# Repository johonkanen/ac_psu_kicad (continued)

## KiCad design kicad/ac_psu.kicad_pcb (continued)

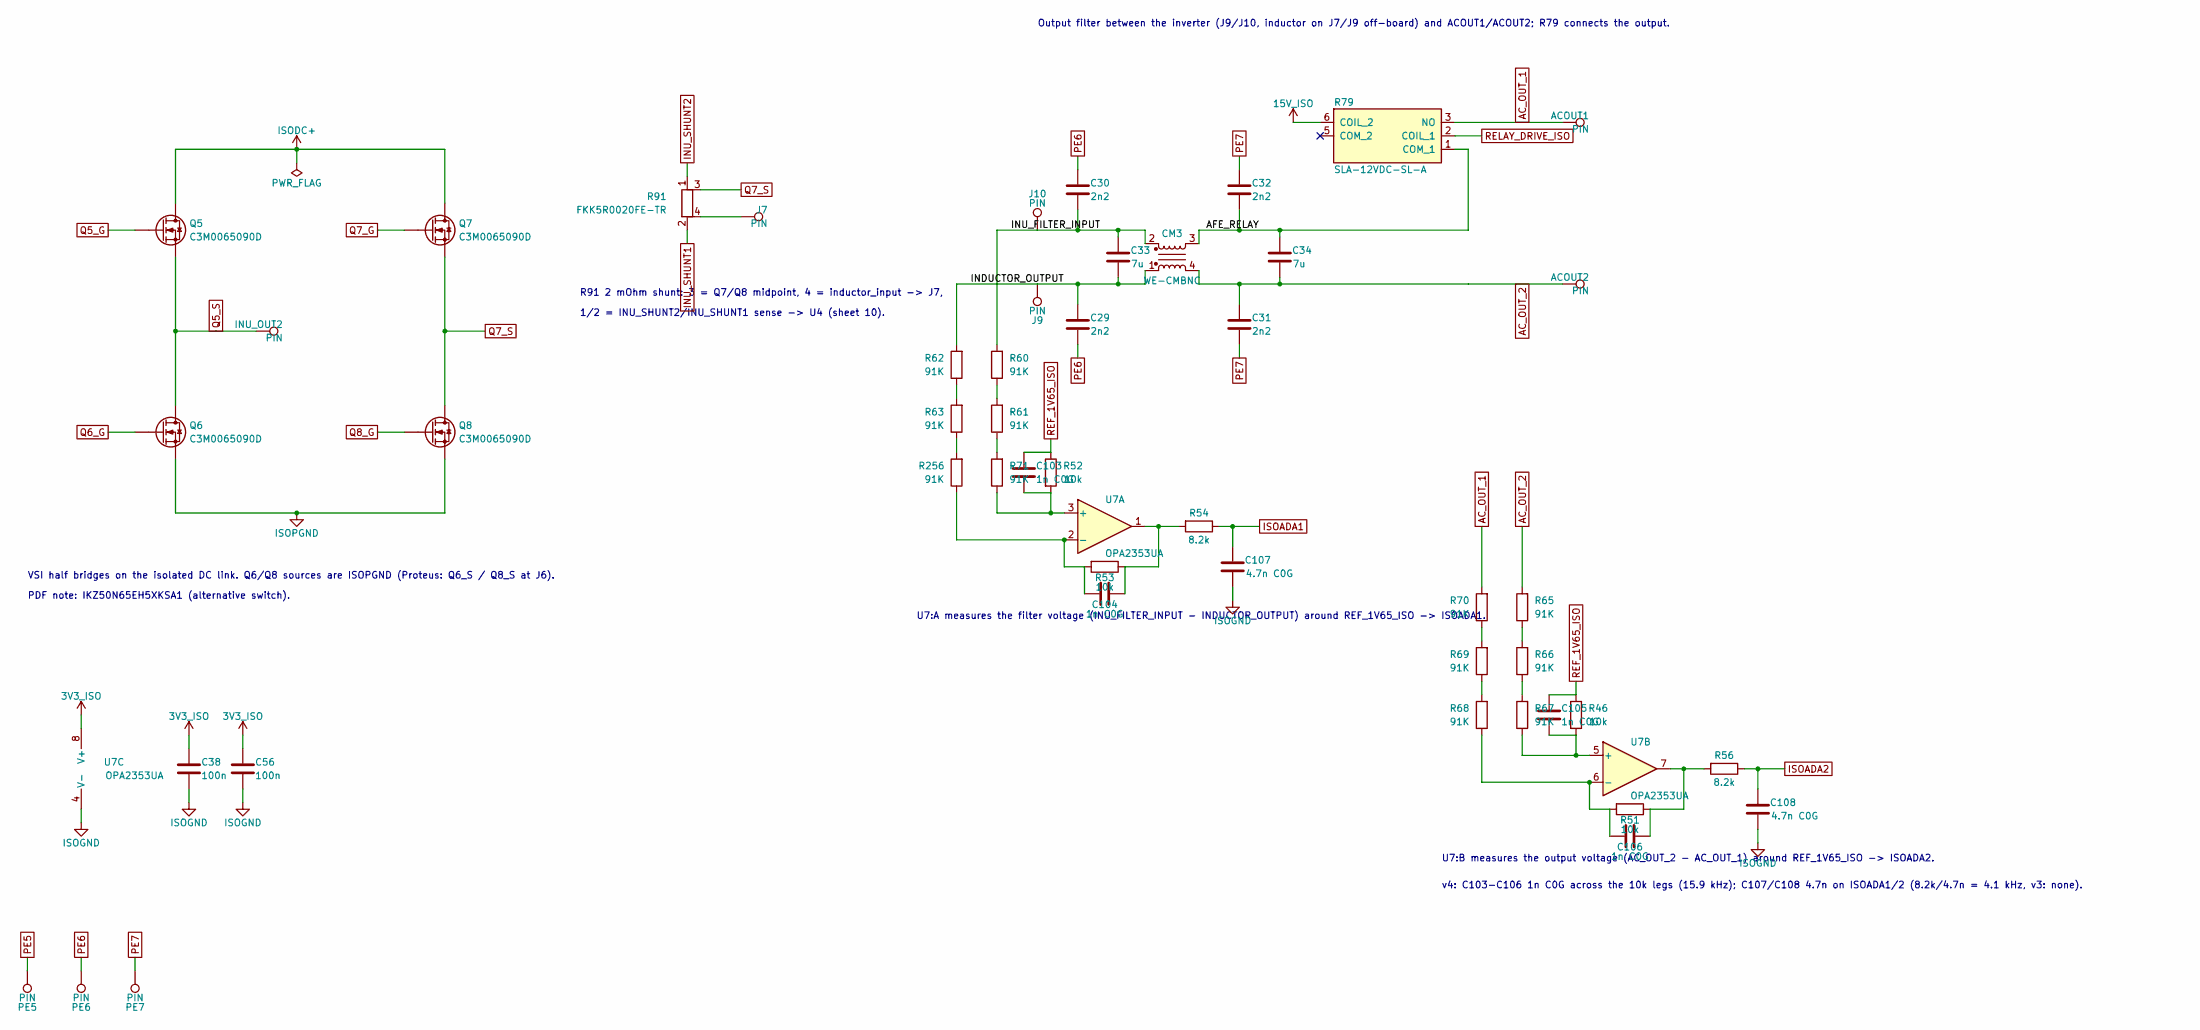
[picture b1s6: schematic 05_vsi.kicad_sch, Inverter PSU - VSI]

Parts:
ACOUT1, ACOUT2: PIN; Terminal_2x1_P5.00mm_D2.0mm_Drill1.4mm
C29, C30, C31, C32: 2n2; C_Disc_D12.5mm_W5.0mm_P7.50mm
C33, C34: 7u; C_Rect_L33.0mm_W20.0mm_P27.50mm_MKS4_Proteus
C38, C56: 100n; C_0402_1005Metric
C103, C104, C105, C106: 1n C0G; C_0402_1005Metric
C107, C108: 4.7n C0G; C_0402_1005Metric
CM3: WE-CMBNC; L_CommonMode_WE-CMBNC
INU_OUT2: PIN; Wuerth_REDCUBE-THR_74650074_M4_PTH
J7, J9, J10: PIN; Wuerth_REDCUBE-THR_74650074_M4_PTH
PE5, PE6, PE7: PIN; Terminal_D4.0mm_Drill3.0mm
Q5, Q6, Q7, Q8: C3M0065090D; TO-247-3_Vertical_Proteus
R46, R51, R52, R53: 10k; R_0402_1005Metric
R54, R56: 8.2k; R_0402_1005Metric
R60, R61, R62, R63, R65, R66, R67, R68, R69, R70, R71, R256: 91K; R_1206_3216Metric_Pad1.30x1.75mm_HandSolder
R79: SLA-12VDC-SL-A; Relay_SLA-12VDC-SL-A
R91: FKK5R0020FE-TR; R_Shunt_FKK5R0020FE
U7: OPA2353UA; TSSOP-8_3x3mm_P0.65mm_Proteus

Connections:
3V3_ISO: C38.2, C56.2, U7.8 (V+); also elsewhere on the board
15V_ISO: R79.6 (COIL_2); also elsewhere on the board
/05 VSI/AFE_RELAY: C32.2, C34.1, CM3.3, R79.1 (COM_1)
/05 VSI/INDUCTOR_OUTPUT: C29.2, C33.2, CM3.1, J9.1, R62.2
/05 VSI/INU_FILTER_INPUT: C30.2, C33.1, CM3.2, J10.1, R60.2
AC_OUT_1: ACOUT1.1, R70.2, R79.3 (NO)
AC_OUT_2: ACOUT2.1, C31.2, C34.2, CM3.4, R65.2
INU_SHUNT1: R91.2; also elsewhere on the board
INU_SHUNT2: R91.1; also elsewhere on the board
ISOADA1: C107.1, R54.1; also elsewhere on the board
ISOADA2: C108.1, R56.1; also elsewhere on the board
ISODC+: Q5.2 (D), Q7.2 (D); also elsewhere on the board
ISOGND: C38.1, C56.1, C107.2, C108.2, U7.4 (V-); also elsewhere on the board
ISOPGND: Q6.3 (S), Q8.3 (S); also elsewhere on the board
unnamed: C104.1, R53.1, R54.2, U7.1
unnamed: C106.1, R51.1, R56.2, U7.7
unnamed: J7.1, R91.4
unnamed: R60.1, R61.2
unnamed: R61.1, R71.2
unnamed: R62.1, R63.2
unnamed: R65.1, R66.2
unnamed: R66.1, R67.2
unnamed: R68.2, R69.1
unnamed: R69.2, R70.1
unnamed: R63.1, R256.2
unnamed: C103.2, R52.2, R71.1, U7.3 (+)
unnamed: C104.2, R53.2, R256.1, U7.2 (-)
unnamed: C105.2, R46.2, R67.1, U7.5 (+)
unnamed: C106.2, R51.2, R68.1, U7.6 (-)
PE5: PE5.1; also elsewhere on the board
PE6: C29.1, C30.1, PE6.1
PE7: C31.1, C32.1, PE7.1
Q5_G: Q5.1 (G); also elsewhere on the board
Q5_S: INU_OUT2.1, Q5.3 (S), Q6.2 (D); also elsewhere on the board
Q6_G: Q6.1 (G); also elsewhere on the board
Q7_G: Q7.1 (G); also elsewhere on the board
Q7_S: Q7.3 (S), Q8.2 (D), R91.3; also elsewhere on the board
Q8_G: Q8.1 (G); also elsewhere on the board
REF_1V65_ISO: C103.1, C105.1, R46.1, R52.1; also elsewhere on the board
RELAY_DRIVE_ISO: R79.2 (COIL_1); also elsewhere on the board

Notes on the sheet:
VSI half bridges on the isolated DC link. Q6/Q8 sources are ISOPGND (Proteus: Q6_S / Q8_S at J6).
PDF note: IKZ50N65EH5XKSA1 (alternative switch).
R91 2 mOhm shunt: 3 = Q7/Q8 midpoint, 4 = inductor_input -> J7,
1/2 = INU_SHUNT2/INU_SHUNT1 sense -> U4 (sheet 10).
Output filter between the inverter (J9/J10, inductor on J7/J9 off-board) and ACOUT1/ACOUT2; R79 connects the output.
U7:A measures the filter voltage (INU_FILTER_INPUT - INDUCTOR_OUTPUT) around REF_1V65_ISO -> ISOADA1.
v4: C103-C106 1n C0G across the 10k legs (15.9 kHz); C107/C108 4.7n on ISOADA1/2 (8.2k/4.7n = 4.1 kHz, v3: none).
U7:B measures the output voltage (AC_OUT_2 - AC_OUT_1) around REF_1V65_ISO -> ISOADA2.

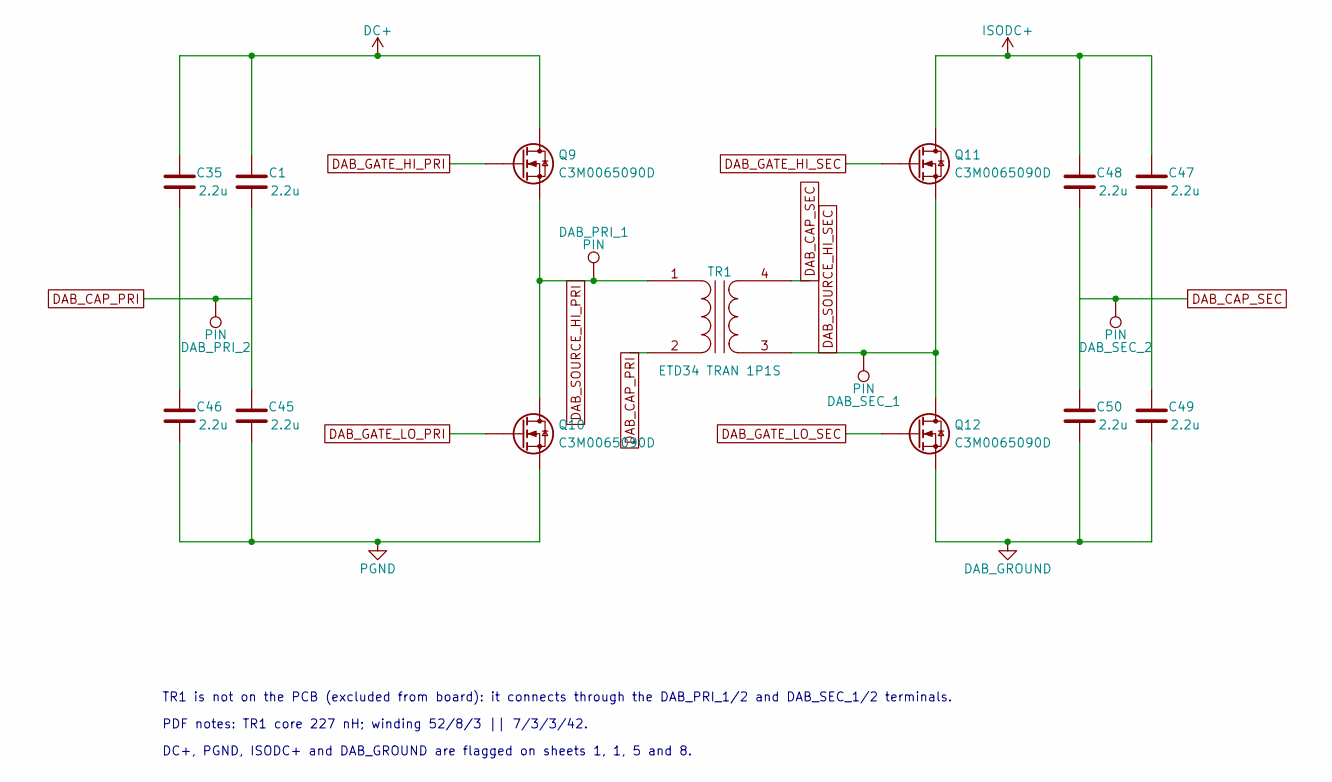
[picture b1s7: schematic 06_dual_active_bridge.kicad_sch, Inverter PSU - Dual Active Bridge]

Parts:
C1, C35, C45, C46, C47, C48, C49, C50: 2.2u; C_2220_5750Metric_Pad1.97x5.40mm_HandSolder
DAB_PRI_1, DAB_PRI_2: PIN; Terminal_D4.0mm_Drill3.0mm
DAB_SEC_1, DAB_SEC_2: PIN; Terminal_D4.0mm_Drill3.0mm
Q9, Q10, Q11, Q12: C3M0065090D; TO-247-3_Vertical_Proteus
TR1: ETD34 TRAN 1P1S

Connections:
DAB_CAP_PRI: C1.2, C35.2, C45.1, C46.1, DAB_PRI_2.1, TR1.2 (AB)
DAB_CAP_SEC: C47.2, C48.2, C49.1, C50.1, DAB_SEC_2.1, TR1.4 (SB)
DAB_GATE_HI_PRI: Q9.1 (G); also elsewhere on the board
DAB_GATE_HI_SEC: Q11.1 (G); also elsewhere on the board
DAB_GATE_LO_PRI: Q10.1 (G); also elsewhere on the board
DAB_GATE_LO_SEC: Q12.1 (G); also elsewhere on the board
DAB_GROUND: C49.2, C50.2, Q12.3 (S); also elsewhere on the board
DAB_SOURCE_HI_PRI: DAB_PRI_1.1, Q9.3 (S), Q10.2 (D), TR1.1 (AA); also elsewhere on the board
DAB_SOURCE_HI_SEC: DAB_SEC_1.1, Q11.3 (S), Q12.2 (D), TR1.3 (SA); also elsewhere on the board
DC+: C1.1, C35.1, Q9.2 (D); also elsewhere on the board
ISODC+: C47.1, C48.1, Q11.2 (D); also elsewhere on the board
PGND: C45.2, C46.2, Q10.3 (S); also elsewhere on the board

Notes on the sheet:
TR1 is not on the PCB (excluded from board): it connects through the DAB_PRI_1/2 and DAB_SEC_1/2 terminals.
PDF notes: TR1 core 227 nH; winding 52/8/3 || 7/3/3/42.
DC+, PGND, ISODC+ and DAB_GROUND are flagged on sheets 1, 1, 5 and 8.

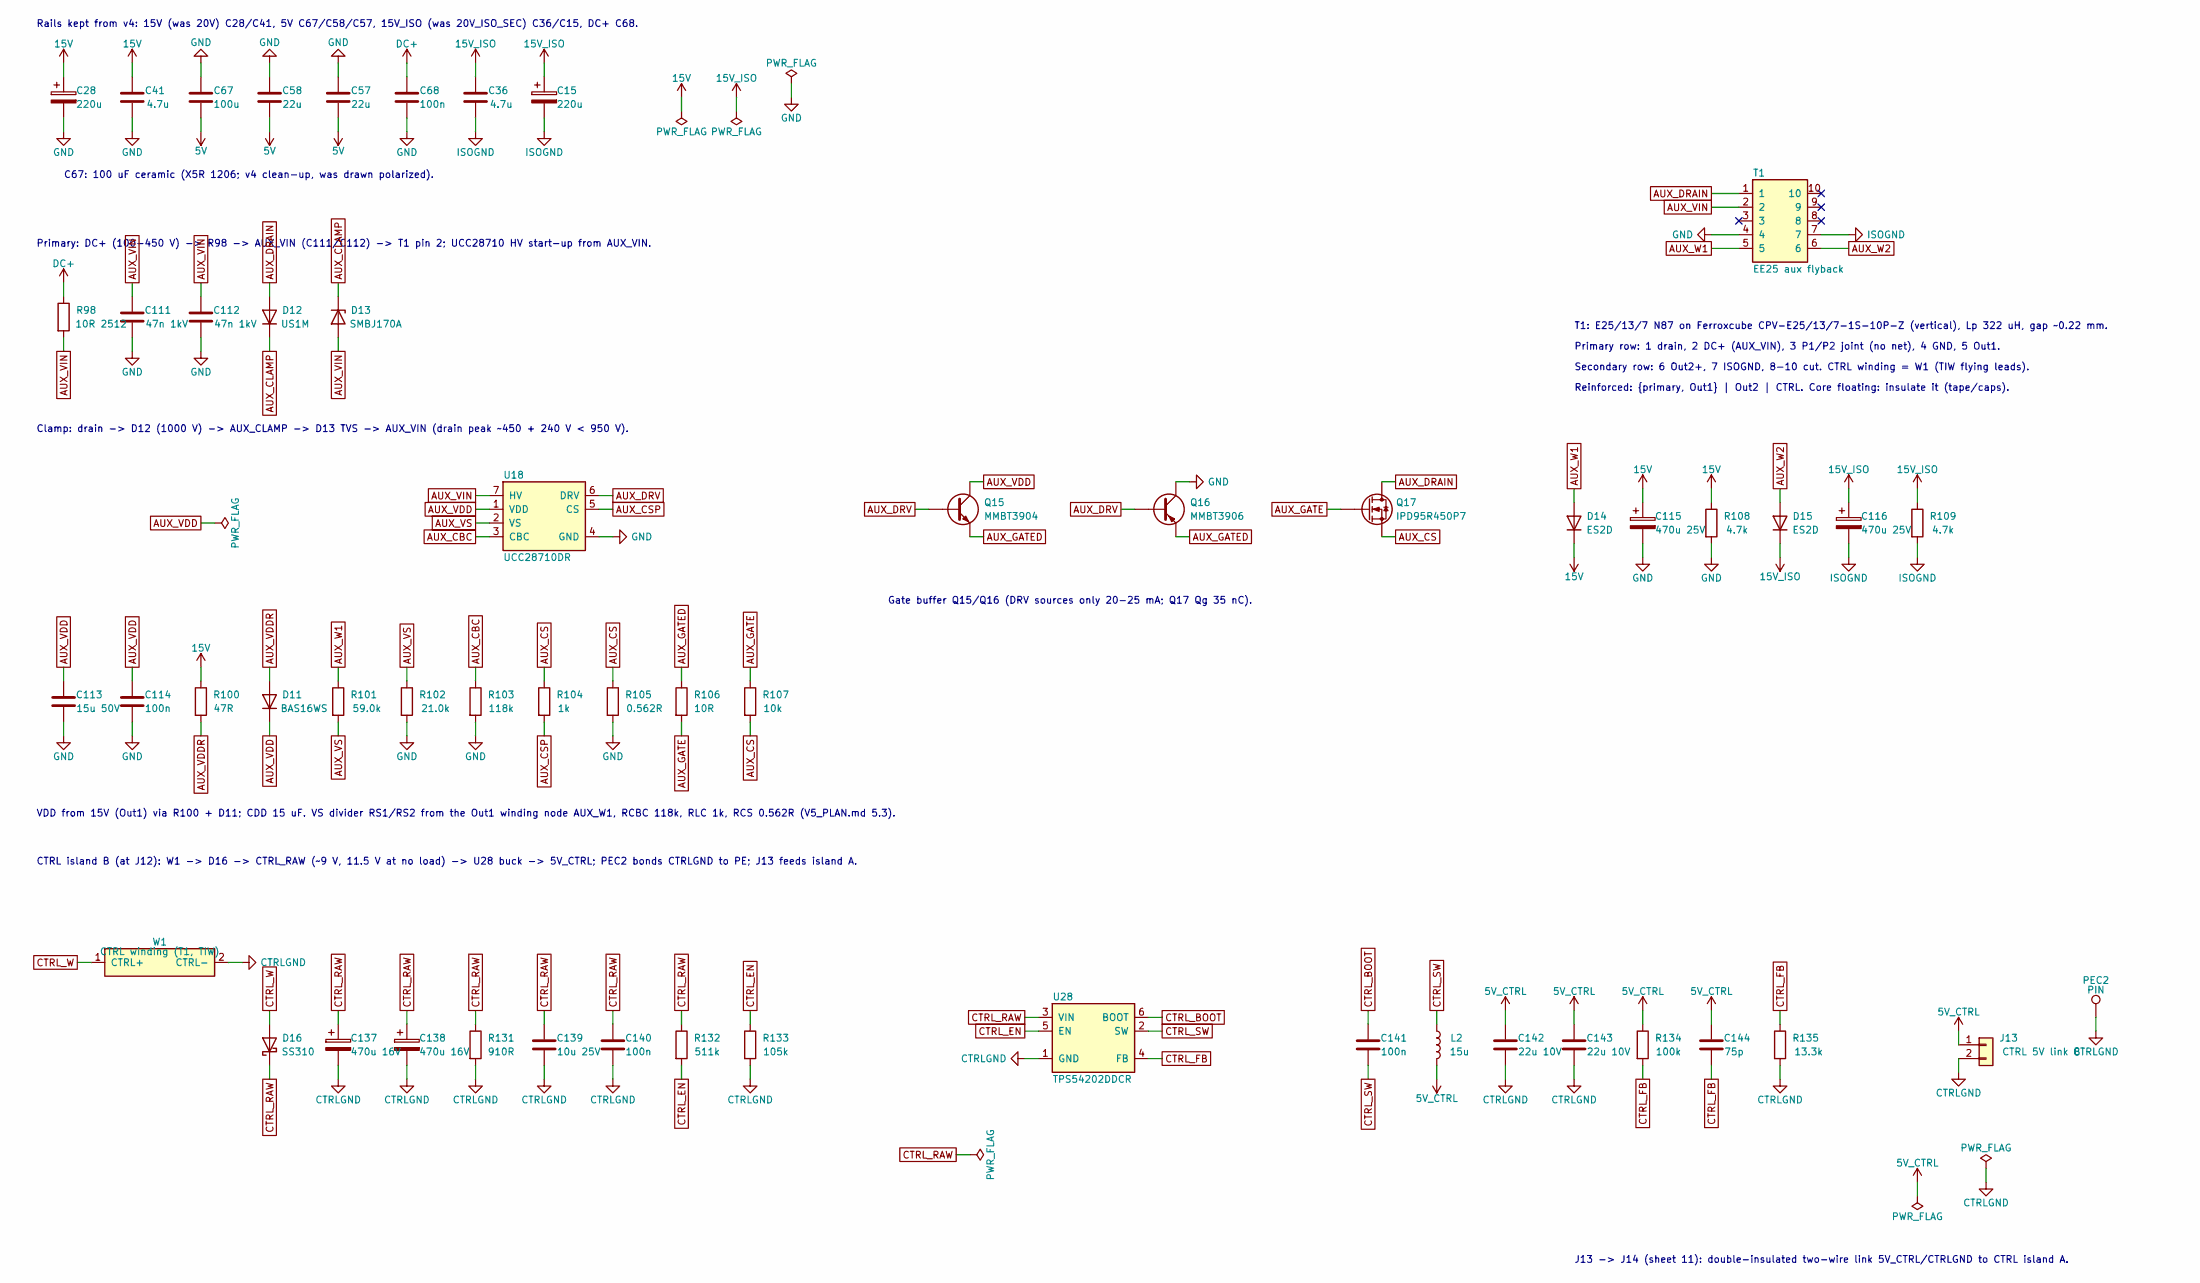
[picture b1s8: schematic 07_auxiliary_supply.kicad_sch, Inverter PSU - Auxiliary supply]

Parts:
C15, C28: 220u; CP_Elec_6.3x7.7_EEEFTE221XAP
C36, C41: 4.7u; C_1206_3216Metric_Pad1.33x1.80mm_HandSolder
C57, C58: 22u; C_1206_3216Metric_Pad1.33x1.80mm_HandSolder
C67: 100u; C_1206_3216Metric_Pad1.33x1.80mm_HandSolder
C68: 100n; C_1206_3216Metric_Pad1.33x1.80mm_HandSolder
C111, C112: 47n 1kV; C_1210_3225Metric
C113: 15u 50V; C_1210_3225Metric
C114, C140, C141: 100n; C_0603_1608Metric
C115, C116: 470u 25V; CP_Elec_8x10
C137, C138: 470u 16V; CP_Elec_8x10
C139: 10u 25V; C_1206_3216Metric
C142, C143: 22u 10V; C_1206_3216Metric
C144: 75p; C_0603_1608Metric
D11: BAS16WS; D_SOD-323_AC
D12: US1M; D_SMA_AC
D13: SMBJ170A; D_SMB_AC
D14, D15: ES2D; D_SMA_AC
D16: SS310; D_SMA_AC
J13: CTRL 5V link B; PinHeader_1x02_P2.54mm_Vertical
L2: 15u; L_Sunlord_SWPA6045S
PEC2: PIN; Terminal_D4.0mm_Drill3.0mm
Q15: MMBT3904; SOT-23
Q16: MMBT3906; SOT-23
Q17: IPD95R450P7; TO-252-2
R98: 10R 2512; R_2512_6332Metric
R100: 47R; R_0603_1608Metric
R101: 59.0k; R_0603_1608Metric
R102: 21.0k; R_0603_1608Metric
R103: 118k; R_0603_1608Metric
R104: 1k; R_0603_1608Metric
R105: 0.562R; R_1206_3216Metric
R106: 10R; R_0603_1608Metric
R107: 10k; R_0603_1608Metric
R108, R109: 4.7k; R_0805_2012Metric
R131: 910R; R_1206_3216Metric
R132: 511k; R_0603_1608Metric
R133: 105k; R_0603_1608Metric
R134: 100k; R_0603_1608Metric
R135: 13.3k; R_0603_1608Metric
T1: EE25 aux flyback; Transformer_EE25_Ferroxcube_CPV-E25-13-7-1S-10P_Vertical
U18: UCC28710DR; SOIC-7_3.9x4.9mm_P1.27mm_UCC28710
U28: TPS54202DDCR; SOT-23-6
W1: CTRL winding (T1, TIW); CTRL_Winding_Leads_2x1.6mm_P5.08mm

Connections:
5V: C57.2, C58.2, C67.2; also elsewhere on the board
5V_CTRL: C142.1, C143.1, C144.1, J13.1, L2.2, R134.1; also elsewhere on the board
15V: C28.1, C41.1, C115.1, D14.C (K), R100.1, R108.1; also elsewhere on the board
15V_ISO: C15.1, C36.1, C116.1, D15.C (K), R109.1; also elsewhere on the board
AUX_CBC: R103.1, U18.3 (CBC)
AUX_CLAMP: D12.C (K), D13.C (K)
AUX_CS: Q17.3 (S), R104.1, R105.1, R107.2
AUX_CSP: R104.2, U18.5 (CS)
AUX_DRAIN: D12.A, Q17.2 (D), T1.1
AUX_DRV: Q15.1 (B), Q16.1 (B), U18.6 (DRV)
AUX_GATE: Q17.1 (G), R106.2, R107.1
AUX_GATED: Q15.2 (E), Q16.2 (E), R106.1
AUX_VDD: C113.1, C114.1, D11.C (K), Q15.3 (C), U18.1 (VDD)
AUX_VDDR: D11.A, R100.2
AUX_VIN: C111.1, C112.1, D13.A, R98.2, T1.2, U18.7 (HV)
AUX_VS: R101.2, R102.1, U18.2 (VS)
AUX_W1: D14.A, R101.1, T1.5
AUX_W2: D15.A, T1.6
CTRLGND: C137.2, C138.2, C139.2, C140.2, C142.2, C143.2, J13.2, PEC2.1, R131.2, R133.2, R135.2, U28.1 (GND), W1.2 (CTRL-); also elsewhere on the board
CTRL_BOOT: C141.1, U28.6 (BOOT)
CTRL_EN: R132.2, R133.1, U28.5 (EN)
CTRL_FB: C144.2, R134.2, R135.1, U28.4 (FB)
CTRL_RAW: C137.1, C138.1, C139.1, C140.1, D16.C (K), R131.1, R132.1, U28.3 (VIN)
CTRL_SW: C141.2, L2.1, U28.2 (SW)
CTRL_W: D16.A, W1.1 (CTRL+)
DC+: C68.2, R98.1; also elsewhere on the board
GND: C28.2, C41.2, C57.1, C58.1, C67.1, C68.1, C111.2, C112.2, C113.2, C114.2, C115.2, Q16.3 (C), R102.2, R103.2, R105.2, R108.2, T1.4, U18.4 (GND); also elsewhere on the board
ISOGND: C15.2, C36.2, C116.2, R109.2, T1.7; also elsewhere on the board

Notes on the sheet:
Rails kept from v4: 15V (was 20V) C28/C41, 5V C67/C58/C57, 15V_ISO (was 20V_ISO_SEC) C36/C15, DC+ C68.
C67: 100 uF ceramic (X5R 1206; v4 clean-up, was drawn polarized).
Primary: DC+ (100-450 V) -> R98 -> AUX_VIN (C111/C112) -> T1 pin 2; UCC28710 HV start-up from AUX_VIN.
Clamp: drain -> D12 (1000 V) -> AUX_CLAMP -> D13 TVS -> AUX_VIN (drain peak ~450 + 240 V < 950 V).
VDD from 15V (Out1) via R100 + D11; CDD 15 uF. VS divider RS1/RS2 from the Out1 winding node AUX_W1, RCBC 118k, RLC 1k, RCS 0.562R (V5_PLAN.md 5.3).
Gate buffer Q15/Q16 (DRV sources only 20-25 mA; Q17 Qg 35 nC).
T1: E25/13/7 N87 on Ferroxcube CPV-E25/13/7-1S-10P-Z (vertical), Lp 322 uH, gap ~0.22 mm.
Primary row: 1 drain, 2 DC+ (AUX_VIN), 3 P1/P2 joint (no net), 4 GND, 5 Out1.
Secondary row: 6 Out2+, 7 ISOGND, 8-10 cut. CTRL winding = W1 (TIW flying leads).
Reinforced: {primary, Out1} | Out2 | CTRL. Core floating: insulate it (tape/caps).
CTRL island B (at J12): W1 -> D16 -> CTRL_RAW (~9 V, 11.5 V at no load) -> U28 buck -> 5V_CTRL; PEC2 bonds CTRLGND to PE; J13 feeds island A.
J13 -> J14 (sheet 11): double-insulated two-wire link 5V_CTRL/CTRLGND to CTRL island A.

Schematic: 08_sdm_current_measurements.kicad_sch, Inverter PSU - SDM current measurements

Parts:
C52, C53, C74, C75: 220p; C_0603_1608Metric
C64, C80: 100n; C_0402_1005Metric
C71, C73, C76, C77: 100n; C_0603_1608Metric
C91, C92: 100n C0G; C_1206_3216Metric
D8: MM3Z5V1T1; D_SOD-323_AC
R55, R72: 33R; R_0402_1005Metric
R57, R58, R73, R74: 12.4R; R_0402_1005Metric
R59, R75: 470R; R_0805_2012Metric_Pad1.20x1.40mm_HandSolder
R64: FKK5R0020FE-TR; R_Shunt_FKK5R0020FE
U5, U6: ADUM7701-8BRIZ-RL7; SOIC-8W_7.5x5.85mm_P1.27mm_ADuM7701

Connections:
3V3_ISO: C80.2, U6.8 (VDD2); also elsewhere on the board
ADCLK: U5.7 (MCLKIN); also elsewhere on the board
ADCLK_DAB: U6.7 (MCLKIN); also elsewhere on the board
DAB_GROUND: R64.4; also elsewhere on the board
DAB_SHUNT1: R64.2, R73.2
DAB_SHUNT2: C74.2, C75.2, C76.2, C77.2, R64.1, R74.2, U6.4 (GND1)
GND: C64.1, U5.5 (GND2); also elsewhere on the board
ISOGND: C80.1, U6.5 (GND2); also elsewhere on the board
ISOPGND: R64.3; also elsewhere on the board
ISO_DAB_SDM_RAW_VOLTAGE: R75.2; also elsewhere on the board
MDATA: R55.2; also elsewhere on the board
MDATA_DAB: R72.2; also elsewhere on the board
unnamed: C71.1, C73.1, D8.C (K), R59.1, U5.1 (VDD1)
unnamed: R55.1, U5.6 (MDAT)
unnamed: C53.1, C91.1, R57.1, U5.2 (VIN+)
unnamed: C52.1, C91.2, R58.1, U5.3 (VIN-)
unnamed: R72.1, U6.6 (MDAT)
unnamed: C76.1, C77.1, R75.1, U6.1 (VDD1)
unnamed: C75.1, C92.1, R73.1, U6.2 (VIN+)
unnamed: C74.1, C92.2, R74.1, U6.3 (VIN-)
SDM_RAW_VOLTAGE: R59.2; also elsewhere on the board
SHUNT1: C52.2, C53.2, C71.2, C73.2, D8.A, R58.2, U5.4 (GND1); also elsewhere on the board
SHUNT2: R57.2; also elsewhere on the board
VCC: C64.2, U5.8 (VDD2); also elsewhere on the board

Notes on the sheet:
v4: C91 100n C0G (1206) across VIN+/VIN- compensates the shunt inductance:
tau = L/R = 2.5 us; with 100 nF use R_leg = 2.5 Ohm per nH of shunt L (4 nH -> 10R, 5 nH -> 12.4R, 6 nH -> 15R).
U5 floats on the AFE shunt R48 (sheet 1): GND1 = SHUNT1 (R48 sense pin 1), VDD1 = 5.1 V from D8 via R59.
v4: C92 100n C0G (1206) across VIN+/VIN- compensates the shunt inductance:
(Proteus shows an unlabelled zener here; it has no refdes and is not in the layout)
U6 floats on the DAB shunt R64: GND1 = DAB_SHUNT2.
R64: 2 mOhm Kelvin shunt between ISOPGND and the DAB secondary ground DAB_GROUND (J4 15-20).

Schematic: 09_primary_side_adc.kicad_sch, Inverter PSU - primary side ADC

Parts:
AD1: ADS7056; X2QFN-8_1.5x1.5mm_P0.5mm_ADS7056
C9: 1n; C_0402_1005Metric
C17, C18: 100n; C_0402_1005Metric
C39: 1u; C_0402_1005Metric
C88, C89: 4.7n C0G; C_0402_1005Metric
L1: 22uH; L_0805_2012Metric
R86: 10R; R_0402_1005Metric
R87: RESISTOR_ARRAY; R_Array_Convex_4x0402_Proteus
U11: SN74LV4051; TSSOP-16_4.4x5mm_P0.65mm_Proteus
U12: TLV316IDBVR; SOT-23-5_TLV316

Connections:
ADA0: U11.15 (X2)
ADA1: U11.14 (X1); also elsewhere on the board
ADA2: C88.1, U11.13 (X0); also elsewhere on the board
ADA3: C89.1, U11.12 (X3); also elsewhere on the board
ADA4: U11.1 (X4)
ADA5: U11.2 (X6)
ADA6: U11.4 (X7)
ADASEL0: U11.11 (A); also elsewhere on the board
ADASEL1: U11.10 (B); also elsewhere on the board
ADASEL2: U11.9 (C); also elsewhere on the board
CLK1: R87.3 (R3.1); also elsewhere on the board
CS1: R87.1 (R1.1); also elsewhere on the board
GND: AD1.5 (GND), AD1.8 (AINM), C9.1, C17.1, C18.1, C39.1, C88.2, C89.2, U11.5 (X5), U11.6 (INH), U11.7 (VEE), U11.8 (VSS), U12.2 (V-); also elsewhere on the board
unnamed: AD1.7 (AINP), C9.2, R86.1
unnamed: AD1.4 (DVDD), AD1.6 (AVDD), C17.2, C18.2, L1.1, U12.5 (V+)
unnamed: AD1.3 (SCLK), R87.6 (R3.2)
unnamed: AD1.2 (SDO), R87.7 (R2.2)
unnamed: AD1.1 (~CS), R87.8 (R1.2)
unnamed: U11.3 (X), U12.3 (+)
unnamed: R86.2, U12.1, U12.4 (-)
SDATA1: R87.2 (R2.1); also elsewhere on the board
VCC: C39.2, L1.2, U11.16 (VDD); also elsewhere on the board

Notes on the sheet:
AGND and DC- in the Proteus schematic are both net GND; 3V3 = VCC.
v4: INH (pin 6) tied to GND (v3: single-pin net DGND, floating).
VDD = 3V3 (VCC), VEE = VSS = AGND (GND).
check logic
v4: C88/C89 4.7n C0G (0402) with R18/R9 8.2k filter ADA2/ADA3 at 4.1 kHz; placed next to U11.
R87:D (pads 4/5) has no net in the Proteus layout.

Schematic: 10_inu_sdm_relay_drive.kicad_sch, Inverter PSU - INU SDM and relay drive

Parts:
C37: 100n; C_0402_1005Metric
C43, C44, C55, C78: 100n; C_0603_1608Metric
C51, C54: 220p; C_0603_1608Metric
C90: 100n C0G; C_1206_3216Metric
D3, D4, D5, D10: ZLLS400TA; D_SOD-323_AC
D9: MM3Z5V1T1; D_SOD-323_AC
Q13, Q14: 2N7000; SOT-23_Proteus
R50: 33R; R_0402_1005Metric
R78, R88, R89, R90: 2.2k; R_0603_1608Metric
R92, R93: 12.4R; R_0402_1005Metric
R94: 470R; R_0805_2012Metric_Pad1.20x1.40mm_HandSolder
U4: ADUM7701-8BRIZ-RL7; SOIC-8W_7.5x5.85mm_P1.27mm_ADuM7701

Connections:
3V3_ISO: C37.2, U4.8 (VDD2); also elsewhere on the board
15V: D10.C (K); also elsewhere on the board
15V_ISO: D4.C (K); also elsewhere on the board
GND: C44.2, Q14.3 (S), R90.2; also elsewhere on the board
GPIO_BYPASS_RLY: R89.2, R90.1; also elsewhere on the board
GPIO_BYPASS_RLY_ISO: R78.2, R88.1; also elsewhere on the board
INU_ADCLK: U4.7 (MCLKIN); also elsewhere on the board
INU_SHUNT1: R92.2; also elsewhere on the board
INU_SHUNT2: C51.2, C54.2, C55.2, C78.2, D9.A, R93.2, U4.4 (GND1); also elsewhere on the board
ISOGND: C37.1, C43.2, Q13.3 (S), R88.2, U4.5 (GND2); also elsewhere on the board
ISO_AFE_SDM_RAW_VOLTAGE: R94.2; also elsewhere on the board
MDATA_INU: R50.2; also elsewhere on the board
unnamed: D3.C (K), D4.A
unnamed: D5.C (K), D10.A
unnamed: C55.1, C78.1, D9.C (K), R94.1, U4.1 (VDD1)
unnamed: C43.1, Q13.2 (G), R78.1
unnamed: C44.1, Q14.2 (G), R89.1
unnamed: R50.1, U4.6 (MDAT)
unnamed: C54.1, C90.1, R92.1, U4.2 (VIN+)
unnamed: C51.1, C90.2, R93.1, U4.3 (VIN-)
RELAY_DRIVE: D5.A, Q14.1 (D); also elsewhere on the board
RELAY_DRIVE_ISO: D3.A, Q13.1 (D); also elsewhere on the board

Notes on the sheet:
v4: C90 100n C0G (1206) across VIN+/VIN- compensates the shunt inductance:
tau = L/R = 2.5 us; with 100 nF use R_leg = 2.5 Ohm per nH of shunt L (4 nH -> 10R, 5 nH -> 12.4R, 6 nH -> 15R).
VDD1/GND1 of U4 float on the INU shunt: VDD1 is 5.1 V from D9 via R94 (Proteus auto-named nets), GND1 = INU_SHUNT2.
Relay drivers: RELAY_DRIVE -> R20 coil (sheet 1), RELAY_DRIVE_ISO -> R79 coil (sheet 5).

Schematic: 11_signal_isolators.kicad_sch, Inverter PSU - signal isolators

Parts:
C81, C82, C83, C84, C85, C86, C117, C118, C119, C120, C121, C122, C123, C124, C125, C126, C127, C128, C132, C133: 100n; C_0402_1005Metric
C129, C130: 4.7n C0G; C_0402_1005Metric
C131: 10n C0G; C_0402_1005Metric
C134: 10n; C_0402_1005Metric
C135: 2.2u; C_0603_1608Metric
C136: 1u; C_0603_1608Metric
J14: CTRL 5V link A; PinHeader_1x02_P2.54mm_Vertical
PEC1: PIN; Terminal_D4.0mm_Drill3.0mm
R22: 39R; R_0402_1005Metric
R110, R112, R114: 6.8k 0.1%; R_0603_1608Metric
R111, R113, R115, R116, R118, R120, R122, R124, R126: 10k 0.1%; R_0603_1608Metric
R117, R119, R121, R123, R125, R127: 24.9k 0.1%; R_0603_1608Metric
R128, R129, R130: 8.2k; R_0402_1005Metric
U13, U15, U17: Si8661BD-B-IS; SOIC-16W_7.5x10.3mm_P1.27mm_Proteus
U16: Si8660BD-B-IS; SOIC-16W_7.5x10.3mm_P1.27mm_Proteus
U19, U20: ISO7760FDWR; SOIC-16W_7.5x10.3mm_P1.27mm
U21: CA-IS3742LW; SOIC-16W_7.5x10.3mm_P1.27mm
U22, U23, U24: AMC1311BDWVR; SOIC-8_7.5x5.85mm_P1.27mm
U25, U26: OPA2350EA; VSSOP-8_3x3mm_P0.65mm
U27: TPS73033DBVT; SOT-23-5

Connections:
3V3_CTRL: C82.2, C83.2, C86.2, C117.1, C119.1, C121.1, C124.1, C126.1, C128.1, C132.1, C133.1, C135.1, U13.1 (VDD1), U15.1 (VDD1), U16.1 (VDD1), U19.1 (VCC1), U20.1 (VCC1), U21.1 (VDDA), U21.7 (ENA), U22.8 (VDD2), U23.8 (VDD2), U24.8 (VDD2), U25.8 (V+), U26.8 (V+), U27.5 (OUT)
3V3_ISO: C118.1, C120.1, C122.1, C123.1, C125.1, C127.1, U19.16 (VCC2), U20.16 (VCC2), U21.10 (ENB), U21.16 (VDDB), U22.1 (VDD1), U23.1 (VDD1), U24.1 (VDD1); also elsewhere on the board
5V_CTRL_A: C136.1, J14.1, U27.1 (IN), U27.3 (EN)
ADASEL0: U15.15 (B1); also elsewhere on the board
ADASEL0_ISO: U15.2 (A1); also elsewhere on the board
ADASEL1: U15.14 (B2); also elsewhere on the board
ADASEL1_ISO: U15.3 (A2); also elsewhere on the board
ADASEL2: U15.13 (B3); also elsewhere on the board
ADASEL2_ISO: U15.4 (A3); also elsewhere on the board
ADCLK: R22.2; also elsewhere on the board
ADCLK_DAB: U21.13 (B2); also elsewhere on the board
ADCLK_DAB_CTRL: U21.4 (A2); also elsewhere on the board
ADCLK_ISO: U15.6 (A5); also elsewhere on the board
CLK1: U13.12 (B4); also elsewhere on the board
CLK1_ISO: U13.5 (A4); also elsewhere on the board
CS1: U13.11 (B5); also elsewhere on the board
CS1_ISO: U13.6 (A5); also elsewhere on the board
CTRLGND_A: C82.1, C83.1, C86.1, C117.2, C119.2, C121.2, C124.2, C126.2, C128.2, C129.2, C130.2, C131.2, C132.2, C133.2, C134.2, C135.2, C136.2, J14.2, PEC1.1, R119.2, R123.2, R127.2, U13.8 (GND1), U15.8 (GND1), U16.8 (GND1), U19.8 (GND1), U20.6 (INE), U20.7 (INF), U20.8 (GND1), U21.2 (GNDA), U21.8 (GNDA), U22.5 (GND2), U23.5 (GND2), U24.5 (GND2), U25.4 (V-), U26.4 (V-), U26.5 (+), U27.2 (GND); also elsewhere on the board
CTRL_NR: C134.1, U27.4 (NR)
DAB_PWM_HI_SEC: U20.14 (OUTB); also elsewhere on the board
DAB_PWM_HI_SEC_CTRL: U20.3 (INB); also elsewhere on the board
DAB_PWM_LO_SEC: U20.13 (OUTC); also elsewhere on the board
DAB_PWM_LO_SEC_CTRL: U20.4 (INC); also elsewhere on the board
DAB_PWM_PRI_HI: U16.14 (B2); also elsewhere on the board
DAB_PWM_PRI_HI_ISO: U16.3 (A2); also elsewhere on the board
DAB_PWM_PRI_LO: U16.15 (B1); also elsewhere on the board
DAB_PWM_PRI_LO_ISO: U16.2 (A1); also elsewhere on the board
GND: C81.1, C84.1, C85.1, U13.9 (GND2), U15.9 (GND2), U16.9 (GND2); also elsewhere on the board
GPIO_BYPASS_RLY: U15.12 (B4); also elsewhere on the board
GPIO_BYPASS_RLY_ISO: U20.12 (OUTD); also elsewhere on the board
GPIO_BYPASS_RLY_ISOLATED: U15.5 (A4); also elsewhere on the board
GPIO_BYPASS_RLY_ISO_CTRL: U20.5 (IND); also elsewhere on the board
INU_ADCLK: U21.14 (B1); also elsewhere on the board
INU_ADCLK_CTRL: U21.3 (A1); also elsewhere on the board
ISOADA1: R110.1; also elsewhere on the board
ISOADA1_AIN: R110.2, R111.1, U22.2 (IN)
ISOADA1_CTRL: C129.1, R128.2; also elsewhere on the board
ISOADA1_M: R116.2, R117.1, U25.2 (-)
ISOADA1_N: R116.1, U22.6 (OUTN)
ISOADA1_OUT: R117.2, R128.1, U25.1
ISOADA1_P: R118.1, U22.7 (OUTP)
ISOADA1_PL: R118.2, R119.1, U25.3 (+)
ISOADA2: R112.1; also elsewhere on the board
ISOADA2_AIN: R112.2, R113.1, U23.2 (IN)
ISOADA2_CTRL: C130.1, R129.2; also elsewhere on the board
ISOADA2_M: R120.2, R121.1, U25.6 (-)
ISOADA2_N: R120.1, U23.6 (OUTN)
ISOADA2_OUT: R121.2, R129.1, U25.7
ISOADA2_P: R122.1, U23.7 (OUTP)
ISOADA2_PL: R122.2, R123.1, U25.5 (+)
ISOADA3: R114.1; also elsewhere on the board
ISOADA3_AIN: R114.2, R115.1, U24.2 (IN)
ISOADA3_CTRL: C131.1, R130.2; also elsewhere on the board
ISOADA3_M: R124.2, R125.1, U26.2 (-)
ISOADA3_N: R124.1, U24.6 (OUTN)
ISOADA3_OUT: R125.2, R130.1, U26.1
ISOADA3_P: R126.1, U24.7 (OUTP)
ISOADA3_PL: R126.2, R127.1, U26.3 (+)
ISOGND: C118.2, C120.2, C122.2, C123.2, C125.2, C127.2, R111.2, R113.2, R115.2, U19.9 (GND2), U20.9 (GND2), U21.9 (GNDB), U21.15 (GNDB), U22.3 (SHTDN), U22.4 (GND1), U23.3 (SHTDN), U23.4 (GND1), U24.3 (SHTDN), U24.4 (GND1); also elsewhere on the board
MDATA: U15.10 (B6); also elsewhere on the board
MDATA_DAB: U21.11 (B4); also elsewhere on the board
MDATA_DAB_CTRL: U21.6 (A4); also elsewhere on the board
MDATA_INU: U21.12 (B3); also elsewhere on the board
MDATA_INU_CTRL: U21.5 (A3); also elsewhere on the board
MDATA_ISO: U15.7 (A6); also elsewhere on the board
unnamed: R22.1, U15.11 (B5)
OPA_SPARE: U26.6 (-), U26.7
PWM_G1: U16.12 (B4); also elsewhere on the board
PWM_G1_ISO: U16.5 (A4); also elsewhere on the board
PWM_G2: U16.11 (B5); also elsewhere on the board
PWM_G2_ISO: U16.6 (A5); also elsewhere on the board
PWM_G3: U16.13 (B3); also elsewhere on the board
PWM_G3_ISO: U16.4 (A3); also elsewhere on the board
PWM_G4: U16.10 (B6); also elsewhere on the board
PWM_G4_ISO: U16.7 (A6); also elsewhere on the board
PWM_Q5: U19.15 (OUTA); also elsewhere on the board
PWM_Q5_CTRL: U19.2 (INA); also elsewhere on the board
PWM_Q6: U19.14 (OUTB); also elsewhere on the board
PWM_Q6_CTRL: U19.3 (INB); also elsewhere on the board
PWM_Q7: U19.13 (OUTC); also elsewhere on the board
PWM_Q7_CTRL: U19.4 (INC); also elsewhere on the board
PWM_Q8: U19.12 (OUTD); also elsewhere on the board
PWM_Q8_CTRL: U19.5 (IND); also elsewhere on the board
PWM_TRANS1: U13.13 (B3); also elsewhere on the board
PWM_TRANS1_ISO: U13.4 (A3); also elsewhere on the board
PWM_TRANS2: U13.14 (B2); also elsewhere on the board
PWM_TRANS2_ISO: U13.3 (A2); also elsewhere on the board
PWM_TRANS3: U13.15 (B1); also elsewhere on the board
PWM_TRANS3_ISO: U13.2 (A1); also elsewhere on the board
PWM_TRANS4: U19.11 (OUTE); also elsewhere on the board
PWM_TRANS4_CTRL: U19.6 (INE); also elsewhere on the board
PWM_TRANS5: U19.10 (OUTF); also elsewhere on the board
PWM_TRANS5_CTRL: U19.7 (INF); also elsewhere on the board
PWM_TRANS6: U20.15 (OUTA); also elsewhere on the board
PWM_TRANS6_CTRL: U20.2 (INA); also elsewhere on the board
SDATA1: U13.10 (B6); also elsewhere on the board
SDATA1_ISO: U13.7 (A6); also elsewhere on the board
VCC: C81.2, C84.2, C85.2, U13.16 (VDD2), U15.16 (VDD2), U16.16 (VDD2); also elsewhere on the board

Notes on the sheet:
U17: spare isolator footprint, not connected (all pins N/C in Proteus).
3V3 / DC- terminals in the Proteus schematic = nets VCC / GND.
v5: the isolated side of U15/U13/U16 is CTRL island A (3V3_CTRL / CTRLGND_A; was 3V3_ISO / ISOGND).
v5 CTRL island A: ISO-side PWMs / relay (U19, U20), U4/U6 sigma-delta lines (U21), ISOADA1-3 (U22-U26). Side 1 = CTRL (J11), side 2 = ISO.
U20 INE/INF unused (tied to CTRLGND_A), OUTE/OUTF open.
U21: clocks CTRL -> ISO (U4/U6 MCLKIN), data ISO -> CTRL; firmware samples MDATA_INU/MDATA_DAB with the same phase offset as MDATA_ISO.
C117/C119/C121: CTRL sides of U19/U20/U21, C118/C120/C122: ISO sides.
ISOADAn (U7/U2 output via 8.2k + filter C, sheets 4/5) -> 6.8k/10k (x0.4, <= 1.32 V) -> AMC1311 (gain 1) ->
difference amp 24.9k/10k (x2.49) -> 8.2k + 4.7n/4.7n/10n -> J11: overall x0.996, 0-3.3 V as before.
U26B spare: + to CTRLGND_A, follower.
J14 <- J13 (sheet 7): 5V_CTRL from island B over a double-insulated two-wire link; PEC1 bonds CTRLGND_A to PE.

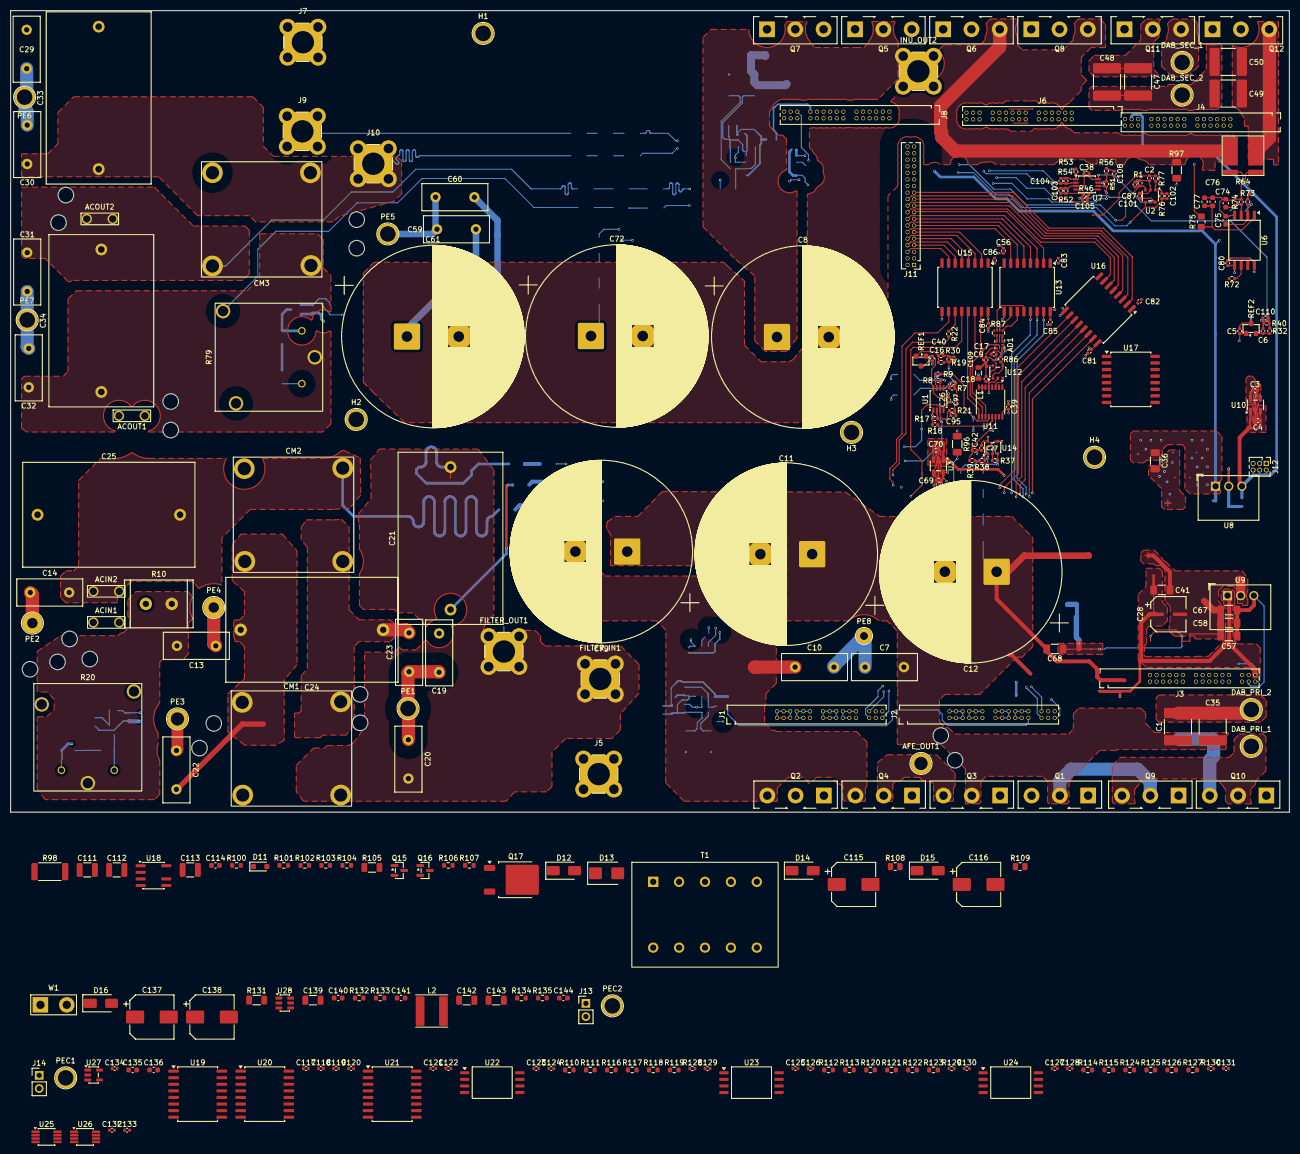
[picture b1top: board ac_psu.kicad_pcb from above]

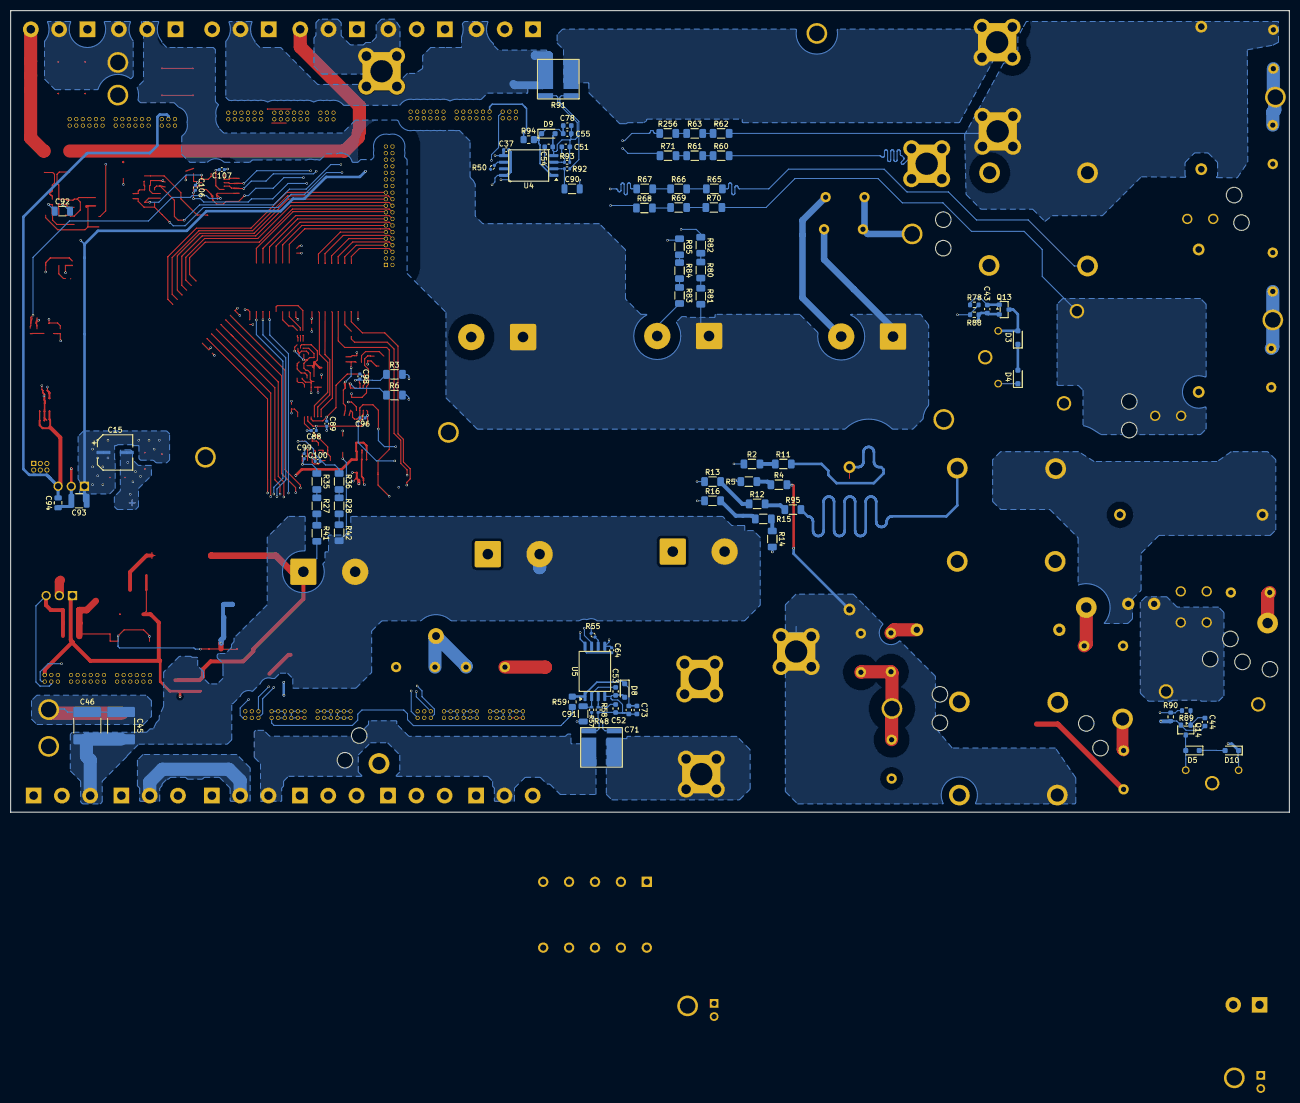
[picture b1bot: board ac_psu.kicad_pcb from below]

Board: 4 copper layers, 246.8 x 154.7 mm, 377 parts (88 on the bottom side), 254 nets.

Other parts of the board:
H1, H2, H3, H4: MountingHole_3.0mm; Terminal_D4.0mm_Drill3.0mm
TIE_ACIN1: cable tie; CableTie_NPTH_2x3.0mm_P5.5mm
TIE_ACOUT1, TIE_ACOUT2: cable tie; CableTie_NPTH_2x3.0mm_P5.5mm
TIE_AFE_OUT1: cable tie; CableTie_NPTH_2x3.0mm_P5.5mm
TIE_PE1, TIE_PE2, TIE_PE3, TIE_PE5: cable tie; CableTie_NPTH_2x3.0mm_P5.5mm
